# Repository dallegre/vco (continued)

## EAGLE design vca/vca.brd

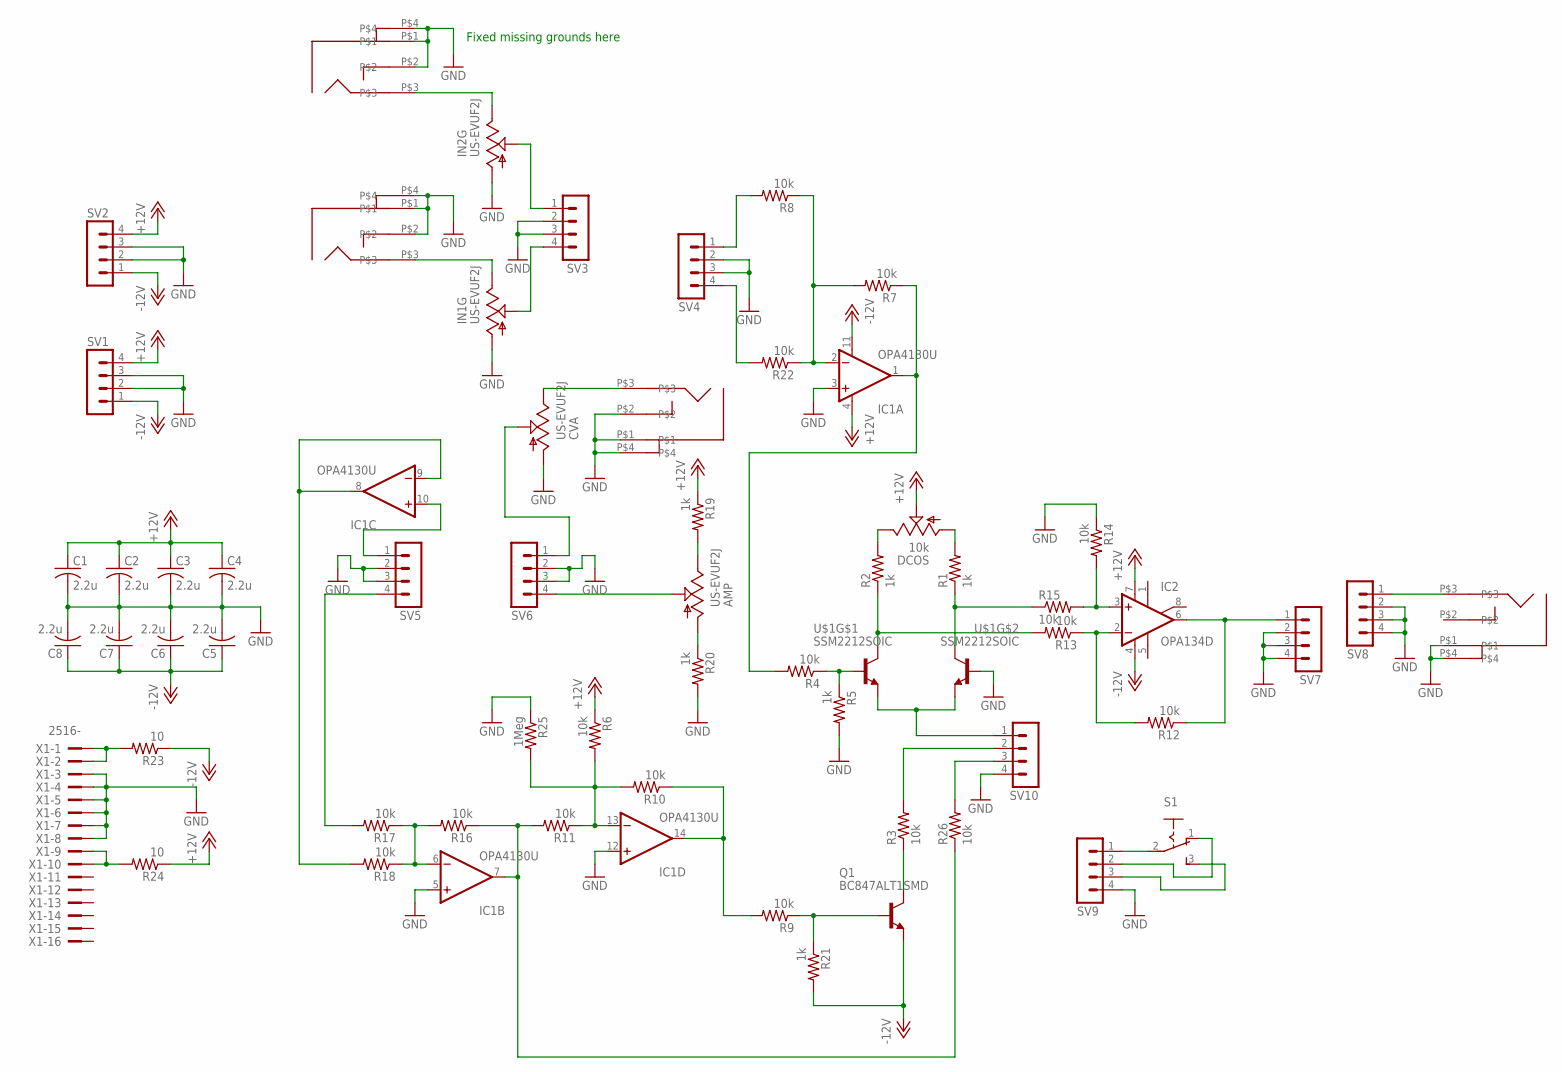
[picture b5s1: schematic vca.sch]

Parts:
AMP: US-EVUF2J; EVUFXJ
C1, C2, C3, C4, C5, C6, C7, C8: 2.2u; C0603
CVA: US-EVUF2J; EVUFXJ
CVIN: PJ301BM
DCOS: 10k; RJ9W
IC1: OPA4130U; SO14
IC2: OPA134D; SO08
IN1, IN2: PJ301BM
IN1G, IN2G: US-EVUF2J; EVUFXJ
OUT: PJ301BM
Q1: BC847ALT1SMD; SOT23
R1, R2, R5, R19, R20, R21: 1k; R0603
R3, R4, R6, R7, R8, R9, R10, R11, R12, R13, R14, R15, R16, R17, R18, R22, R26: 10k; R0603
R23, R24: 10; R0603
R25: 1Meg; R0603
S1: 255SB
SV1, SV2, SV3, SV4, SV5, SV6, SV7, SV8, SV9, SV10: MA04-1
U$1: SSM2212SOIC; SO08
X1: 2516-; PAK100/2500-16

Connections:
+12V: C1.1, C2.1, C3.1, C4.1, DCOS.S, IC1.4 (V+), IC2.7 (V+), R6.1, R19.1, R24.1, SV1.4, SV2.4
-12V: C5.1, C6.1, C7.1, C8.1, IC1.11 (V-), IC2.4 (V-), Q1.2 (E), R21.2, R23.1, SV1.1, SV2.1
GND: C1.2, C2.2, C3.2, C4.2, C5.2, C6.2, C7.2, C8.2, CVA.1 (A), CVIN.P$1, CVIN.P$2, CVIN.P$4, IC1.3 (+IN), IC1.5 (+IN), IC1.12 (+IN), IN1.P$1, IN1.P$2, IN1.P$4, IN1G.1 (A), IN2.P$1, IN2.P$2, IN2.P$4, IN2G.1 (A), OUT.P$1, OUT.P$4, R5.2, R14.1, R20.2, R25.1, SV1.2, SV1.3, SV2.2, SV2.3, SV3.2, SV3.3, SV4.2, SV4.3, SV5.2, SV5.3, SV6.2, SV6.3, SV7.2, SV7.3, SV7.4, SV8.2, SV8.3, SV8.4, SV9.4, SV10.4, U$1.7 (B), X1.3, X1.4, X1.5, X1.6, X1.7, X1.8
unnamed: SV10.1, U$1.3 (E), U$1.6 (E)
unnamed: R4.1, R5.1, U$1.2 (B)
unnamed: R2.1, R13.2, U$1.1 (C)
unnamed: R1.1, R15.1, U$1.8 (C)
unnamed: OUT.P$3, SV8.1
unnamed: IC1.8 (OUT), IC1.9 (-IN), R18.2
unnamed: Q1.3 (C), R3.1
unnamed: Q1.1 (B), R9.1, R21.1
unnamed: IC1.14 (OUT), R9.2, R10.1
unnamed: IC1.2 (-IN), R7.2, R8.1, R22.1
unnamed: IC1.1 (OUT), R4.2, R7.1
unnamed: IC1.13 (-IN), R6.2, R10.2, R11.1, R25.2
unnamed: IC2.3 (+IN), R14.2, R15.2
unnamed: DCOS.E, R2.2
unnamed: DCOS.A, R1.2
unnamed: IC2.2 (-IN), R12.2, R13.1
unnamed: IC2.6 (OUT), R12.1, SV7.1
unnamed: IN2G.2 (S), SV3.1
unnamed: IC1.6 (-IN), R16.2, R17.1, R18.1
unnamed: IN1G.2 (S), SV3.4
unnamed: AMP.3 (E), R19.2
unnamed: AMP.1 (A), R20.1
unnamed: R17.2, SV5.4
unnamed: IN1.P$3, IN1G.3 (E)
unnamed: CVA.3 (E), CVIN.P$3
unnamed: IN2.P$3, IN2G.3 (E)
unnamed: R8.2, SV4.1
unnamed: R22.2, SV4.4
unnamed: R23.2, X1.1, X1.2
unnamed: CVA.2 (S), SV6.1
unnamed: AMP.2 (S), SV6.4
unnamed: IC1.10 (+IN), SV5.1
unnamed: R24.2, X1.9, X1.10
unnamed: R3.2, SV10.2
unnamed: IC1.7 (OUT), R11.2, R16.1, R26.1
unnamed: S1.2, SV9.1
unnamed: R26.2, SV10.3
unnamed: S1.1 (O), SV9.2
unnamed: S1.3 (S), SV9.3

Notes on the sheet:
Fixed missing grounds here

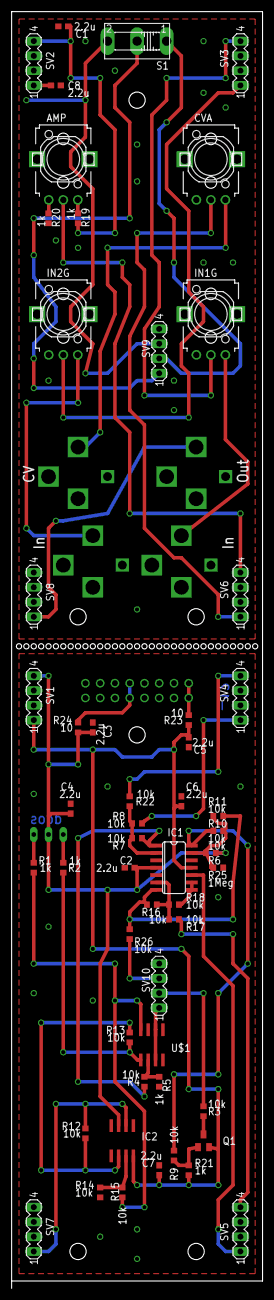
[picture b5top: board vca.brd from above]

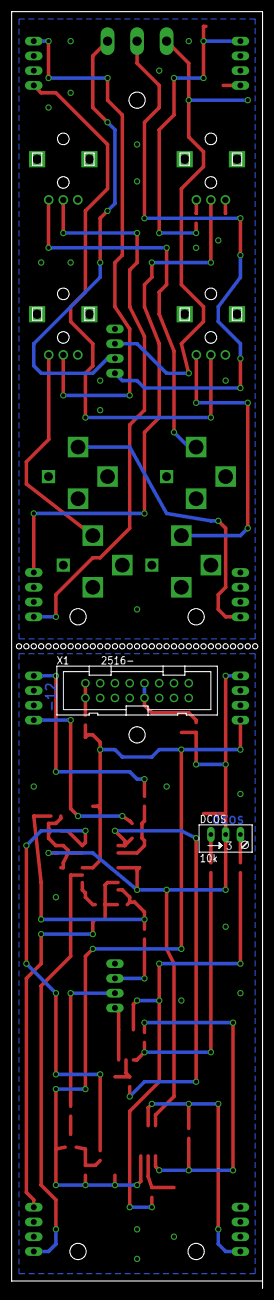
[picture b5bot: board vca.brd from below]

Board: 2 copper layers, 43.2 x 219.7 mm, 59 parts (2 on the bottom side), 42 nets.

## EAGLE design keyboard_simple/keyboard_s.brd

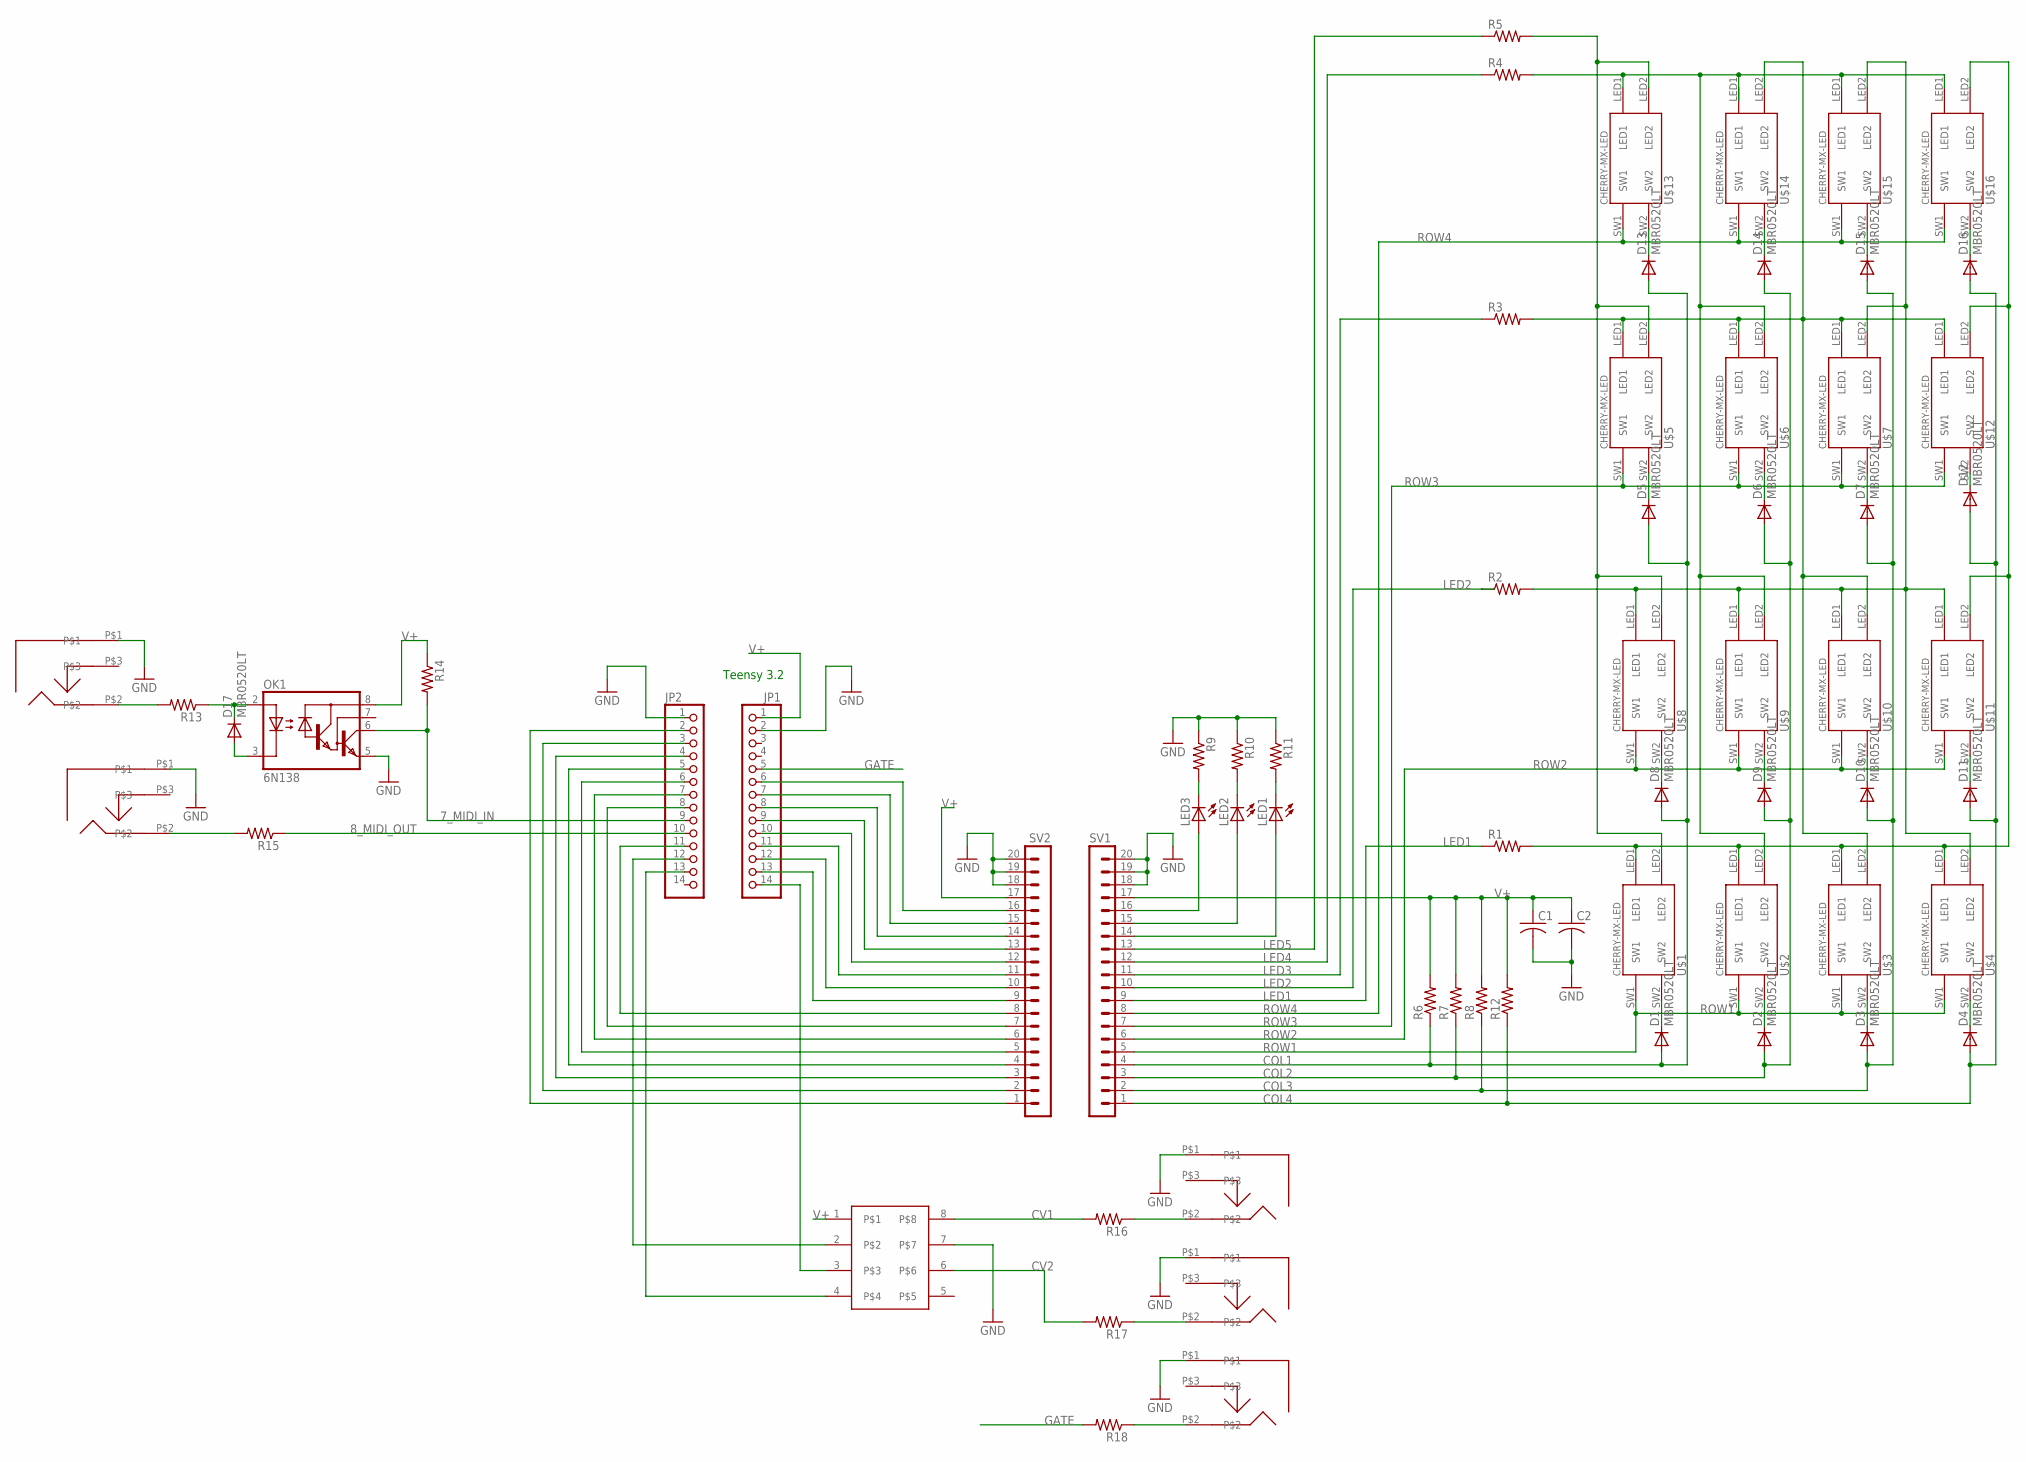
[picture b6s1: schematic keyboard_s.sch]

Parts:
C1, C2: C-USC0603; C0603
D1, D2, D3, D4, D5, D6, D7, D8, D9, D10, D11, D12, D13, D14, D15, D16, D17: MBR0520LT; SOD123
JP1, JP2: PINHD-1X14; 1X14
LED1, LED2, LED3: LED5MM
OK1: 6N138; DIL08
R1, R2, R3, R4, R5, R6, R7, R8, R9, R10, R11, R12, R13, R14, R15, R16, R17, R18: R-US_R0603; R0603
SV1, SV2: MA20-1
U$1, U$2, U$3, U$4, U$5, U$6, U$7, U$8, U$9, U$10, U$11, U$12, U$13, U$14, U$15, U$16: CHERRY-MX-LED
U$17: MCP4822; SO08
U$18, U$19, U$20, U$21, U$22: MJ3536N

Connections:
7_MIDI_IN: JP2.9, OK1.6 (VO), R14.2
8_MIDI_OUT: JP2.10, R15.1
COL1: D1.A, D5.A, D8.A, D13.A, R6.1, SV1.4
COL2: D2.A, D6.A, D9.A, D14.A, R7.1, SV1.3
COL3: D3.A, D7.A, D10.A, D15.A, R8.1, SV1.2
COL4: D4.A, D11.A, D12.A, D16.A, R12.1, SV1.1
CV1: R16.2, U$17.8
CV2: R17.2, U$17.6
GATE: JP1.5, R18.2
GND: C1.2, C2.2, JP1.2, JP2.1, OK1.5 (GND), R9.1, R10.1, R11.1, SV1.18, SV1.19, SV1.20, SV2.18, SV2.19, SV2.20, U$17.7, U$18.P$1, U$19.P$1, U$20.P$1, U$21.P$1, U$22.P$1
LED1: R1.1, SV1.9
LED2: R2.1, SV1.10
LED3: R3.1, SV1.11
LED4: R4.1, SV1.12
LED5: R5.1, SV1.13
unnamed: D8.C, U$8.SW2
unnamed: D9.C, U$9.SW2
unnamed: D10.C, U$10.SW2
unnamed: D11.C, U$11.SW2
unnamed: D12.C, U$12.SW2
unnamed: D13.C, U$13.SW2
unnamed: D14.C, U$14.SW2
unnamed: D7.C, U$7.SW2
unnamed: D6.C, U$6.SW2
unnamed: D5.C, U$5.SW2
unnamed: D4.C, U$4.SW2
unnamed: D3.C, U$3.SW2
unnamed: D2.C, U$2.SW2
unnamed: D1.C, U$1.SW2
unnamed: D15.C, U$15.SW2
unnamed: D16.C, U$16.SW2
unnamed: LED1.A, SV1.14
unnamed: D17.C, OK1.2 (A), R13.1
unnamed: R1.2, U$1.LED1, U$2.LED1, U$3.LED1, U$4.LED1, U$11.LED2, U$12.LED2, U$16.LED2
unnamed: D17.A, OK1.3 (C)
unnamed: LED2.A, SV1.15
unnamed: LED3.A, SV1.16
unnamed: R13.2, U$18.P$2
unnamed: JP1.14, U$17.3
unnamed: JP2.13, U$17.4
unnamed: JP2.12, U$17.2
unnamed: JP2.2, SV2.1
unnamed: JP2.3, SV2.2
unnamed: JP2.4, SV2.3
unnamed: JP2.5, SV2.4
unnamed: JP2.6, SV2.5
unnamed: JP2.7, SV2.6
unnamed: JP2.8, SV2.7
unnamed: JP2.11, SV2.8
unnamed: JP1.13, SV2.9
unnamed: JP1.12, SV2.10
unnamed: JP1.11, SV2.11
unnamed: JP1.10, SV2.12
unnamed: JP1.9, SV2.13
unnamed: JP1.8, SV2.14
unnamed: JP1.7, SV2.15
unnamed: JP1.6, SV2.16
unnamed: R15.2, U$19.P$2
unnamed: R16.1, U$20.P$2
unnamed: R17.1, U$21.P$2
unnamed: R18.1, U$22.P$2
unnamed: LED1.K (C), R11.2
unnamed: R3.2, U$3.LED2, U$5.LED1, U$6.LED1, U$7.LED1, U$10.LED2, U$12.LED1, U$14.LED2
unnamed: R5.2, U$1.LED2, U$5.LED2, U$8.LED2, U$13.LED2
unnamed: LED2.K (C), R10.2
unnamed: LED3.K (C), R9.2
unnamed: R4.2, U$2.LED2, U$6.LED2, U$9.LED2, U$13.LED1, U$15.LED1, U$16.LED1
unnamed: R2.2, U$4.LED2, U$7.LED2, U$8.LED1, U$9.LED1, U$10.LED1, U$11.LED1, U$15.LED2
ROW1: SV1.5, U$1.SW1, U$2.SW1, U$3.SW1, U$4.SW1
ROW2: SV1.6, U$8.SW1, U$9.SW1, U$10.SW1, U$11.SW1
ROW3: SV1.7, U$5.SW1, U$6.SW1, U$7.SW1, U$12.SW1
ROW4: SV1.8, U$13.SW1, U$14.SW1, U$15.SW1, U$16.SW1
V+: C1.1, C2.1, JP1.1, OK1.8 (VCC), R6.2, R7.2, R8.2, R12.2, R14.1, SV1.17, SV2.17

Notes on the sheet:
Teensy 3.2

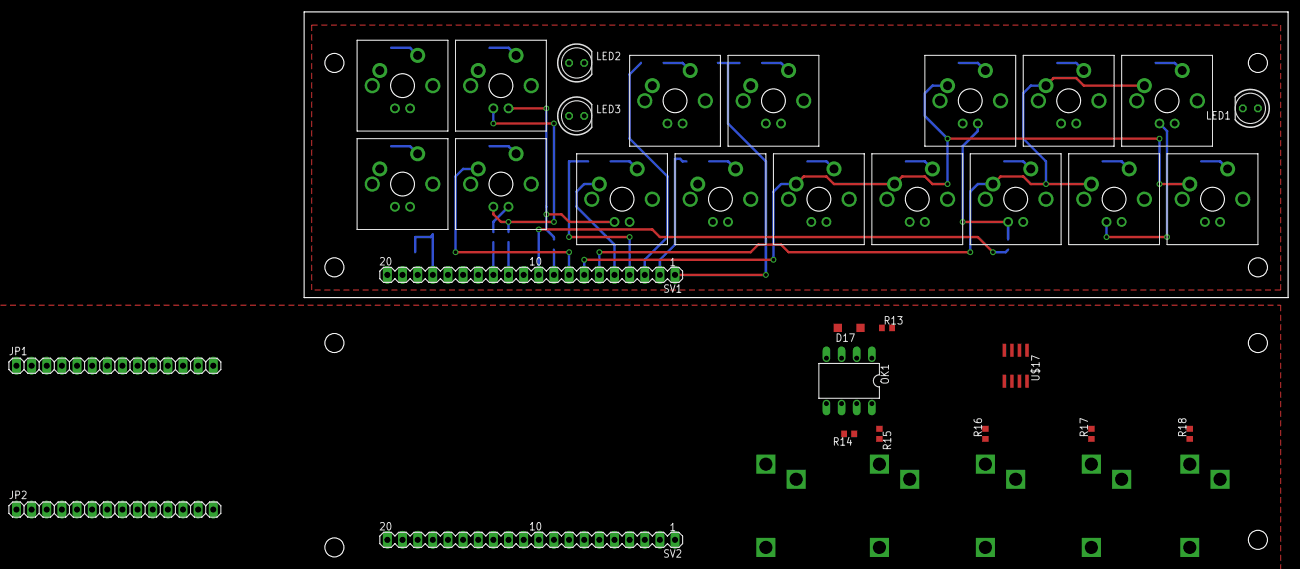
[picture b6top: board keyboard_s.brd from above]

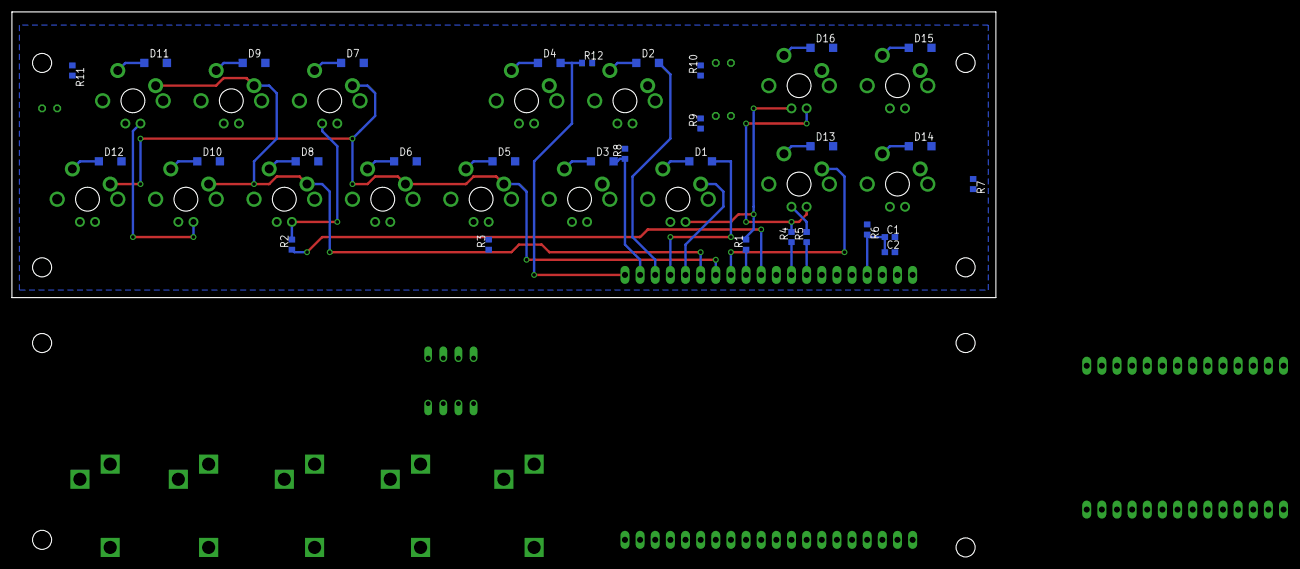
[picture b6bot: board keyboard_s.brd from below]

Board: 2 copper layers, 165.1 x 47.9 mm, 67 parts (30 on the bottom side), 73 nets.

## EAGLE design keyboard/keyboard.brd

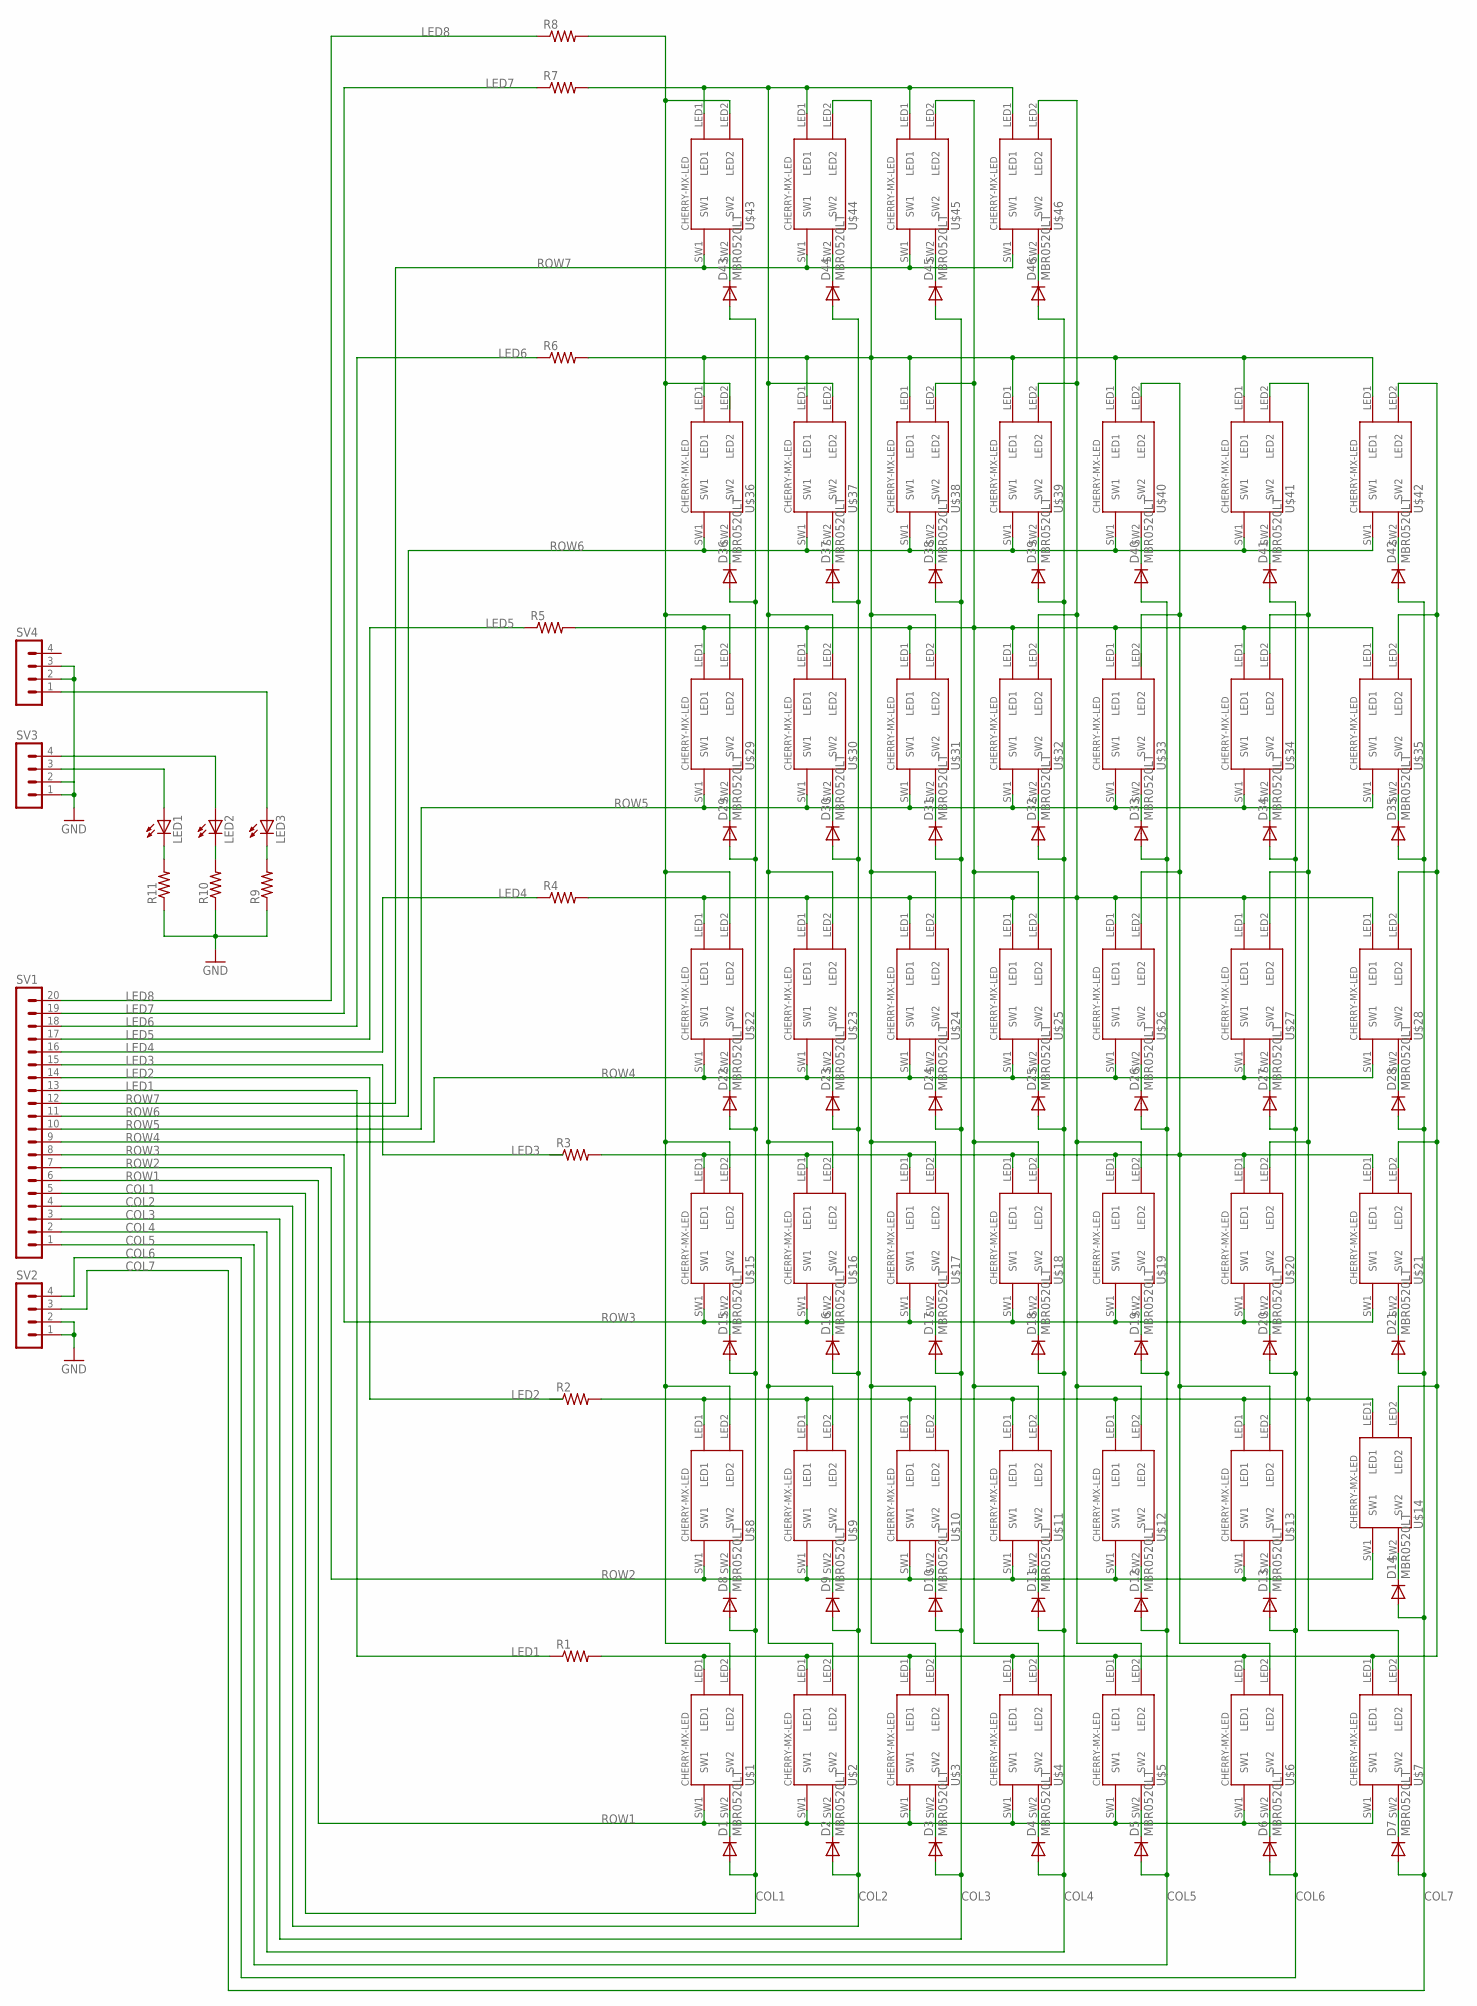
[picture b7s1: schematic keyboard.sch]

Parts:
D1, D2, D3, D4, D5, D6, D7, D8, D9, D10, D11, D12, D13, D14, D15, D16, D17, D18, D19, D20, D21, D22, D23, D24, D25, D26, D27, D28, D29, D30, D31, D32, D33, D34, D35, D36, D37, D38, D39, D40, D41, D42, D43, D44, D45, D46: MBR0520LT; SOD123
LED1, LED2, LED3: LED5MM
R1, R2, R3, R4, R5, R6, R7, R8, R9, R10, R11: R-US_R0603; R0603
SV1: MA20-1
SV2, SV3, SV4: MA04-1
U$1, U$2, U$3, U$4, U$5, U$6, U$7, U$8, U$9, U$10, U$11, U$12, U$13, U$14, U$15, U$16, U$17, U$18, U$19, U$20, U$21, U$22, U$23, U$24, U$25, U$26, U$27, U$28, U$29, U$30, U$31, U$32, U$33, U$34, U$35, U$36, U$37, U$38, U$39, U$40, U$41, U$42, U$43, U$44, U$45, U$46: CHERRY-MX-LED

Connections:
COL1: D1.A, D8.A, D15.A, D22.A, D29.A, D36.A, D43.A, SV1.5
COL2: D2.A, D9.A, D16.A, D23.A, D30.A, D37.A, D44.A, SV1.4
COL3: D3.A, D10.A, D17.A, D24.A, D31.A, D38.A, D45.A, SV1.3
COL4: D4.A, D11.A, D18.A, D25.A, D32.A, D39.A, D46.A, SV1.2
COL5: D5.A, D12.A, D19.A, D26.A, D33.A, D40.A, SV1.1
COL6: D6.A, D13.A, D20.A, D27.A, D34.A, D41.A
COL7: D7.A, D14.A, D21.A, D28.A, D35.A, D42.A, SV2.3
GND: R9.1, R10.1, R11.1, SV2.1, SV2.2, SV3.1, SV3.2, SV4.2, SV4.3
LED1: R1.1, SV1.13
LED2: SV1.14
LED3: SV1.15
LED4: R4.1, SV1.16
LED5: R5.1, SV1.17
LED6: R6.1, SV1.18
LED7: R7.1, SV1.19
LED8: R8.1, SV1.20
unnamed: D8.C, U$8.SW2
unnamed: D9.C, U$9.SW2
unnamed: D10.C, U$10.SW2
unnamed: D11.C, U$11.SW2
unnamed: D12.C, U$12.SW2
unnamed: D13.C, U$13.SW2
unnamed: D14.C, U$14.SW2
unnamed: D7.C, U$7.SW2
unnamed: D6.C, U$6.SW2
unnamed: D5.C, U$5.SW2
unnamed: D4.C, U$4.SW2
unnamed: D3.C, U$3.SW2
unnamed: D2.C, U$2.SW2
unnamed: D1.C, U$1.SW2
unnamed: D15.C, U$15.SW2
unnamed: D16.C, U$16.SW2
unnamed: D17.C, U$17.SW2
unnamed: D18.C, U$18.SW2
unnamed: D19.C, U$19.SW2
unnamed: D20.C, U$20.SW2
unnamed: D21.C, U$21.SW2
unnamed: D27.C, U$27.SW2
unnamed: D28.C, U$28.SW2
unnamed: D29.C, U$29.SW2
unnamed: D30.C, U$30.SW2
unnamed: D31.C, U$31.SW2
unnamed: D32.C, U$32.SW2
unnamed: D33.C, U$33.SW2
unnamed: D34.C, U$34.SW2
unnamed: D35.C, U$35.SW2
unnamed: D36.C, U$36.SW2
unnamed: D37.C, U$37.SW2
unnamed: D38.C, U$38.SW2
unnamed: D39.C, U$39.SW2
unnamed: D40.C, U$40.SW2
unnamed: D41.C, U$41.SW2
unnamed: D42.C, U$42.SW2
unnamed: D43.C, U$43.SW2
unnamed: D44.C, U$44.SW2
unnamed: D45.C, U$45.SW2
unnamed: D46.C, U$46.SW2
unnamed: LED1.K (C), R11.2
unnamed: R8.2, U$1.LED2, U$8.LED2, U$15.LED2, U$22.LED2, U$29.LED2, U$43.LED2
unnamed: R1.2, U$1.LED1, U$2.LED1, U$3.LED1, U$4.LED1, U$5.LED1, U$6.LED1, U$7.LED1, U$14.LED2, U$21.LED2, U$28.LED2, U$35.LED2, U$42.LED2
unnamed: R4.2, U$5.LED2, U$12.LED2, U$19.LED2, U$22.LED1, U$23.LED1, U$24.LED1, U$25.LED1, U$26.LED1, U$27.LED1, U$28.LED1, U$32.LED2, U$39.LED2, U$46.LED2
unnamed: R5.2, U$4.LED2, U$11.LED2, U$18.LED2, U$25.LED2, U$29.LED1, U$30.LED1, U$31.LED1, U$32.LED1, U$33.LED1, U$34.LED1, U$35.LED1, U$38.LED2, U$45.LED2
unnamed: R6.2, U$3.LED2, U$10.LED2, U$17.LED2, U$24.LED2, U$31.LED2, U$36.LED1, U$37.LED1, U$38.LED1, U$39.LED1, U$40.LED1, U$41.LED1, U$42.LED1, U$44.LED2
unnamed: LED2.K (C), R10.2
unnamed: LED3.K (C), R9.2
unnamed: LED1.A, SV3.3
unnamed: LED2.A, SV3.4
unnamed: LED3.A, SV4.1
unnamed: R7.2, U$2.LED2, U$9.LED2, U$16.LED2, U$23.LED2, U$30.LED2, U$37.LED2, U$43.LED1, U$44.LED1, U$45.LED1, U$46.LED1
unnamed: R2.2, U$7.LED2, U$8.LED1, U$9.LED1, U$10.LED1, U$11.LED1, U$13.LED1, U$14.LED1, U$20.LED2, U$27.LED2, U$34.LED2, U$41.LED2
unnamed: R3.2, U$6.LED2, U$13.LED2, U$15.LED1, U$16.LED1, U$17.LED1, U$18.LED1, U$19.LED1, U$20.LED1, U$21.LED1, U$26.LED2, U$40.LED2
ROW1: SV1.6, U$1.SW1, U$2.SW1, U$3.SW1, U$4.SW1, U$5.SW1, U$6.SW1, U$7.SW1
ROW2: SV1.7, U$8.SW1, U$9.SW1, U$10.SW1, U$11.SW1, U$12.SW1, U$13.SW1, U$14.SW1
ROW3: SV1.8, U$15.SW1, U$16.SW1, U$17.SW1, U$18.SW1, U$19.SW1, U$20.SW1, U$21.SW1
ROW4: SV1.9, U$22.SW1, U$23.SW1, U$24.SW1, U$25.SW1, U$26.SW1, U$27.SW1, U$28.SW1
ROW5: SV1.10, U$29.SW1, U$30.SW1, U$31.SW1, U$32.SW1, U$33.SW1, U$34.SW1, U$35.SW1
ROW6: SV1.11, U$36.SW1, U$37.SW1, U$38.SW1, U$39.SW1, U$40.SW1, U$41.SW1, U$42.SW1
ROW7: SV1.12, U$43.SW1, U$44.SW1, U$45.SW1, U$46.SW1

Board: 2 copper layers, 110 parts (57 on the bottom side), 76 nets, no tracks yet.

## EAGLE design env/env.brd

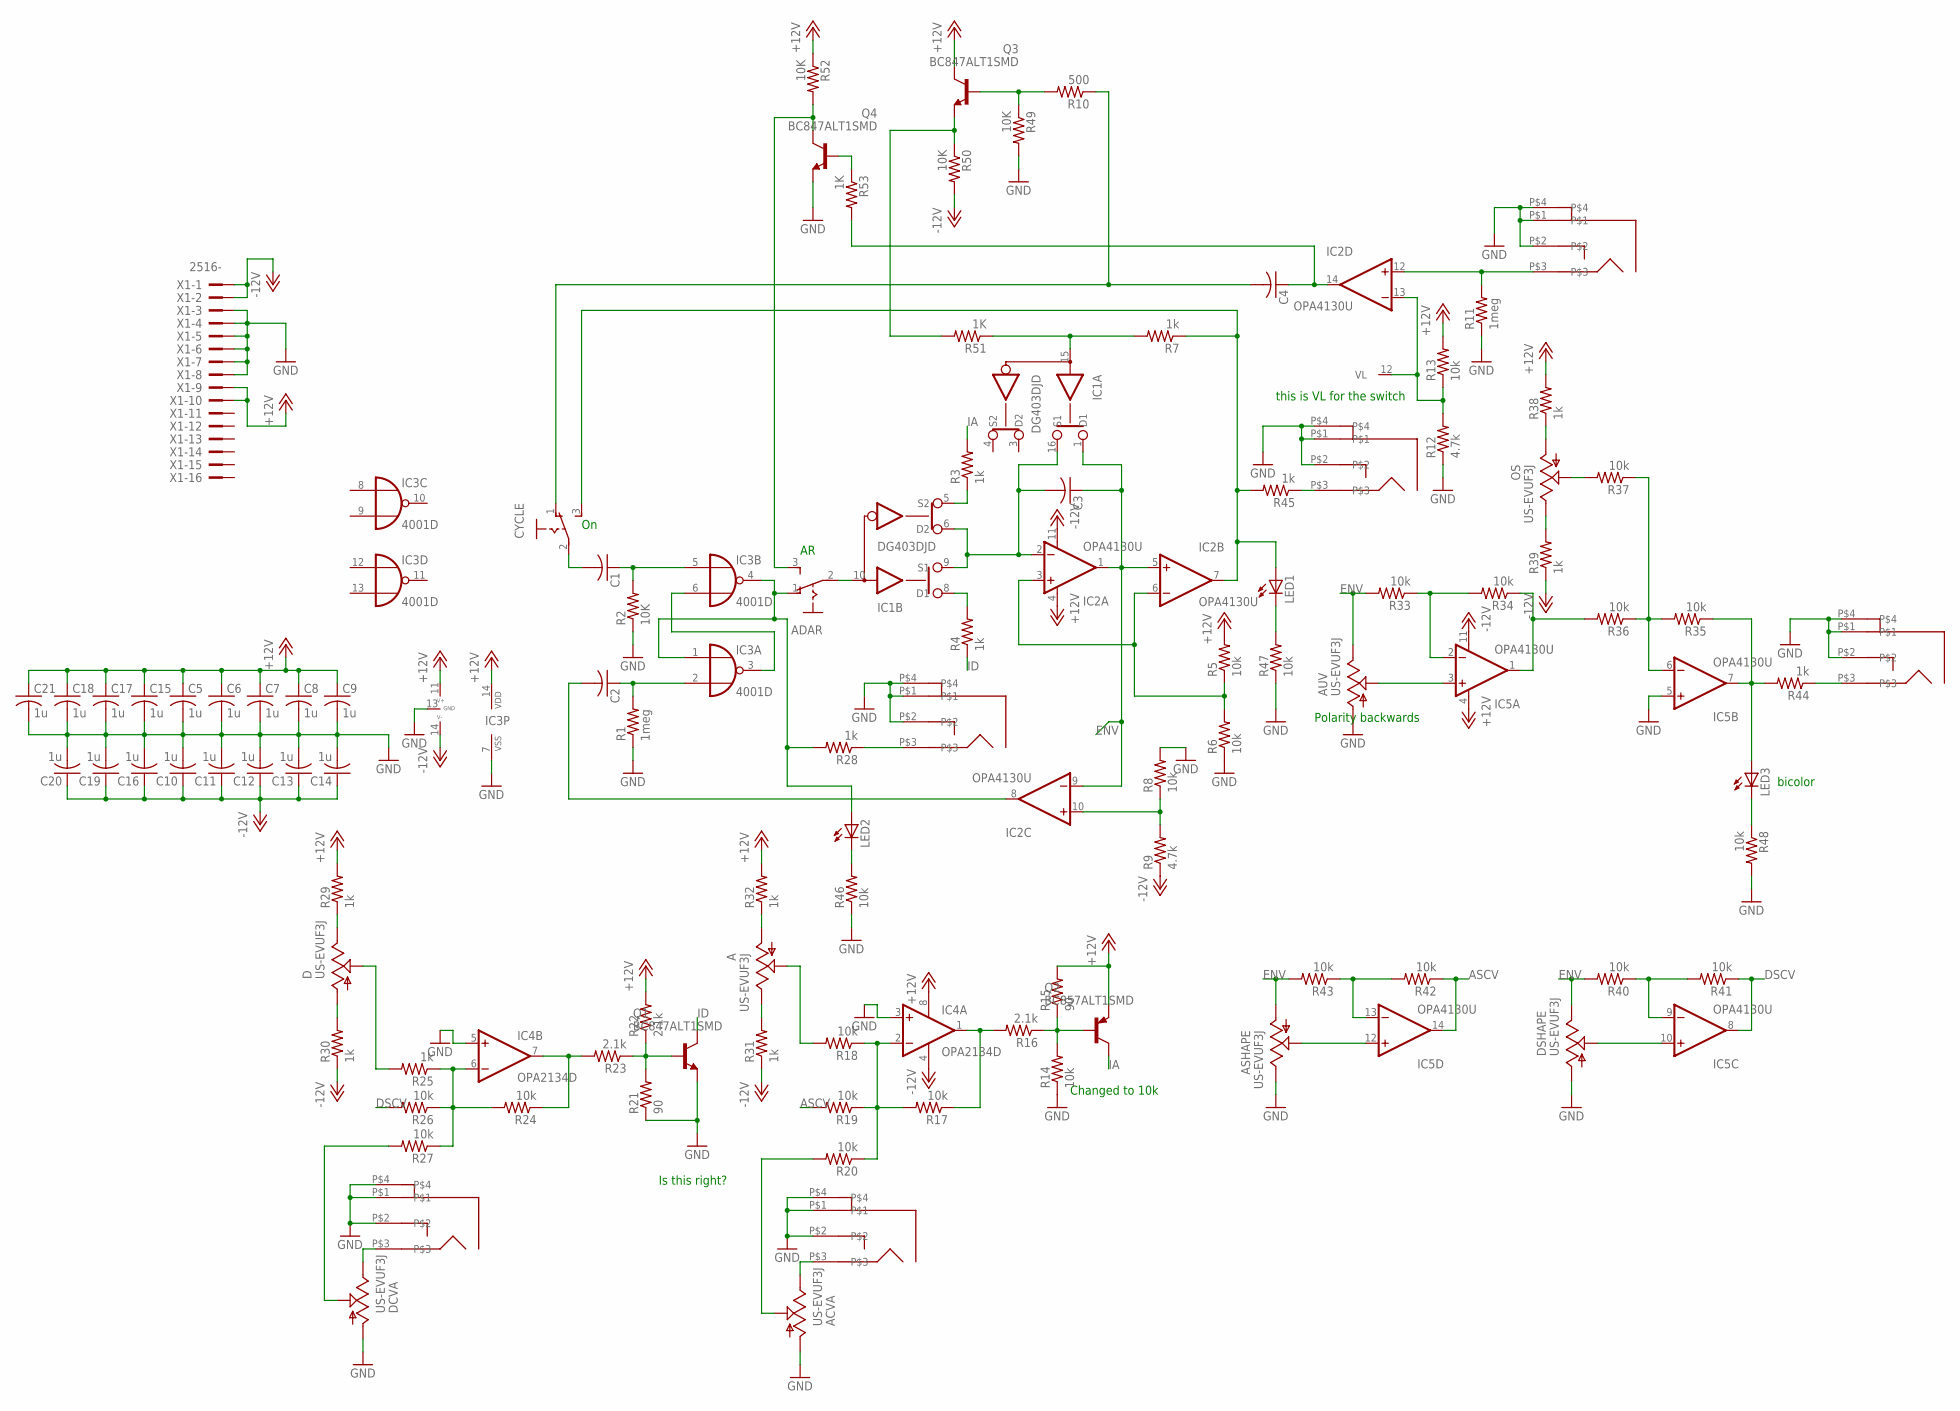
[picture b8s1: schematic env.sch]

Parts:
A: US-EVUF3J; EVUFXJ
ACV: PJ301BM
ACVA: US-EVUF3J; EVUFXJ
ADAR: 255SB
ASHAPE: US-EVUF3J; EVUFXJ
AUV: US-EVUF3J; EVUFXJ
C1, C2, C3, C4: C-USC0603; C0603
C5, C6, C7, C8, C9, C10, C11, C12, C13, C14, C15, C16, C17, C18, C19, C20, C21: 1u; C0603
CVOUT: PJ301BM
CYCLE: 255SB
D: US-EVUF3J; EVUFXJ
DCV: PJ301BM
DCVA: US-EVUF3J; EVUFXJ
DSHAPE: US-EVUF3J; EVUFXJ
EOF: PJ301BM
EOR: PJ301BM
GATE: PJ301BM
IC1: DG403DJD; SO16
IC2, IC5: OPA4130U; SO14
IC3: 4001D; SO14
IC4: OPA2134D; SOIC8
LED1, LED2, LED3: LED5MM
OS: US-EVUF3J; EVUFXJ
Q1, Q3, Q4: BC847ALT1SMD; SOT23
Q2: BC857ALT1SMD; SOT23-BEC
R1, R11: 1meg; R0603
R2, R49, R50, R52: 10K; R0603
R3, R4, R7, R25, R28, R29, R30, R31, R32, R38, R39, R44, R45: 1k; R0603
R5, R6, R8, R13, R14, R17, R18, R19, R20, R24, R26, R27, R33, R34, R35, R36, R37, R40, R41, R42, R43, R46, R47, R48: 10k; R0603
R9, R12: 4.7k; R0603
R10: 500; R0603
R15, R21: 90; R0603
R16, R22, R23: 2.1k; R0603
R51, R53: 1K; R0603
X1: 2516-; PAK100/2500-16

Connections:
+12V: C5.1, C6.1, C7.1, C8.1, C9.1, C15.1, C17.1, C18.1, C21.1, IC1.11 (V+), IC2.4 (V+), IC3.14 (VDD), IC4.8 (V+), IC5.4 (V+), Q2.E, Q3.3 (C), R5.2, R13.2, R15.2, R22.2, R29.2, R32.2, R38.2, R52.1, X1.9, X1.10
-12V: C10.1, C11.1, C12.1, C13.1, C14.1, C16.1, C19.1, C20.1, IC1.14 (V-), IC2.11 (V-), IC4.4 (V-), IC5.11 (V-), R9.1, R30.1, R31.1, R39.1, R50.2, X1.1, X1.2
ASCV: IC5.14 (OUT), R19.2, R42.1
DSCV: IC5.8 (OUT), R26.2, R41.1
ENV: ASHAPE.1 (A), AUV.3 (E), C3.1, DSHAPE.3 (E), IC1.1 (D1), IC2.1 (OUT), IC2.5 (+IN), IC2.9 (-IN), R33.2, R40.2, R43.2
GND: ACV.P$1, ACV.P$2, ACV.P$4, ACVA.1 (A), ASHAPE.3 (E), AUV.1 (A), C5.2, C6.2, C7.2, C8.2, C9.2, C10.2, C11.2, C12.2, C13.2, C14.2, C15.2, C16.2, C17.2, C18.2, C19.2, C20.2, C21.2, CVOUT.P$1, CVOUT.P$2, CVOUT.P$4, DCV.P$1, DCV.P$2, DCV.P$4, DCVA.1 (A), DSHAPE.1 (A), EOF.P$1, EOF.P$2, EOF.P$4, EOR.P$1, EOR.P$2, EOR.P$4, GATE.P$1, GATE.P$2, GATE.P$4, IC1.13 (GND), IC3.7 (VSS), IC4.3 (+IN), IC4.5 (+IN), IC5.5 (+IN), Q1.2 (E), Q4.2 (E), R1.1, R2.1, R6.1, R8.2, R11.1, R12.1, R14.1, R21.1, R46.1, R47.1, R48.2, R49.2, X1.3, X1.4, X1.5, X1.6, X1.7, X1.8
IA: Q2.C, R3.2
ID: Q1.3 (C), R4.1
unnamed: IC3.3 (O), IC3.6 (I1)
unnamed: ADAR.1 (O), IC3.1 (I0), IC3.4 (O), LED2.A, R28.2
unnamed: C2.1, IC3.2 (I1), R1.2
unnamed: C1.1, IC3.5 (I0), R2.2
unnamed: C3.2, IC1.6 (D2), IC1.9 (S1), IC1.16 (S1), IC2.2 (-IN)
unnamed: IC1.8 (D1), R4.2
unnamed: IC1.5 (S2), R3.1
unnamed: IC2.10 (+IN), R8.1, R9.2
unnamed: CYCLE.3 (S), IC2.7 (OUT), LED1.A, R7.1, R45.2
unnamed: AUV.2 (S), IC5.3 (+IN)
unnamed: Q3.2 (E), R50.1, R51.2
unnamed: C2.2, IC2.8 (OUT)
unnamed: IC2.3 (+IN), IC2.6 (-IN), R5.1, R6.2
unnamed: ADAR.3 (S), Q4.3 (C), R52.2
unnamed: Q2.B, R14.2, R15.1, R16.1
unnamed: GATE.P$3, IC2.12 (+IN), R11.2
unnamed: IC1.12 (VL), IC2.13 (-IN), R12.2, R13.1
unnamed: ADAR.2, IC1.10 (IN)
unnamed: C1.2, CYCLE.2
unnamed: C4.1, IC2.14 (OUT), R53.2
unnamed: IC4.1 (OUT), R16.2, R17.1
unnamed: IC4.7 (OUT), R23.2, R24.1
unnamed: IC4.2 (-IN), R17.2, R18.1, R19.1, R20.1
unnamed: IC4.6 (-IN), R24.2, R25.1, R26.1, R27.1
unnamed: D.3 (E), R29.1
unnamed: Q1.1 (B), R21.2, R22.1, R23.1
unnamed: IC5.6 (-IN), R35.2, R36.1, R37.1
unnamed: A.1 (A), R32.1
unnamed: D.1 (A), R30.2
unnamed: A.3 (E), R31.2
unnamed: D.2 (S), R25.2
unnamed: A.2 (S), R18.2
unnamed: IC5.1 (OUT), R34.1, R36.2
unnamed: IC5.2 (-IN), R33.1, R34.2
unnamed: CVOUT.P$3, R44.1
unnamed: IC5.7 (OUT), LED3.A, R35.1, R44.2
unnamed: OS.1 (A), R38.1
unnamed: ACV.P$3, ACVA.3 (E)
unnamed: OS.3 (E), R39.2
unnamed: OS.2 (S), R37.2
unnamed: IC5.13 (-IN), R42.2, R43.1
unnamed: IC5.9 (-IN), R40.1, R41.2
unnamed: LED2.K (C), R46.2
unnamed: DCV.P$3, DCVA.3 (E)
unnamed: ASHAPE.2 (S), IC5.12 (+IN)
unnamed: DCVA.2 (S), R27.2
unnamed: EOR.P$3, R28.1
unnamed: DSHAPE.2 (S), IC5.10 (+IN)
unnamed: EOF.P$3, R45.1
unnamed: ACVA.2 (S), R20.2
unnamed: Q3.1 (B), R10.2, R49.1
unnamed: LED1.K (C), R47.2
unnamed: IC1.15 (IN), R7.2, R51.1
unnamed: C4.2, CYCLE.1 (O), R10.1
unnamed: Q4.1 (B), R53.1
unnamed: LED3.K (C), R48.1

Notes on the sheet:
Is this right?
Changed to 10k
Polarity backwards
bicolor
this is VL for the switch

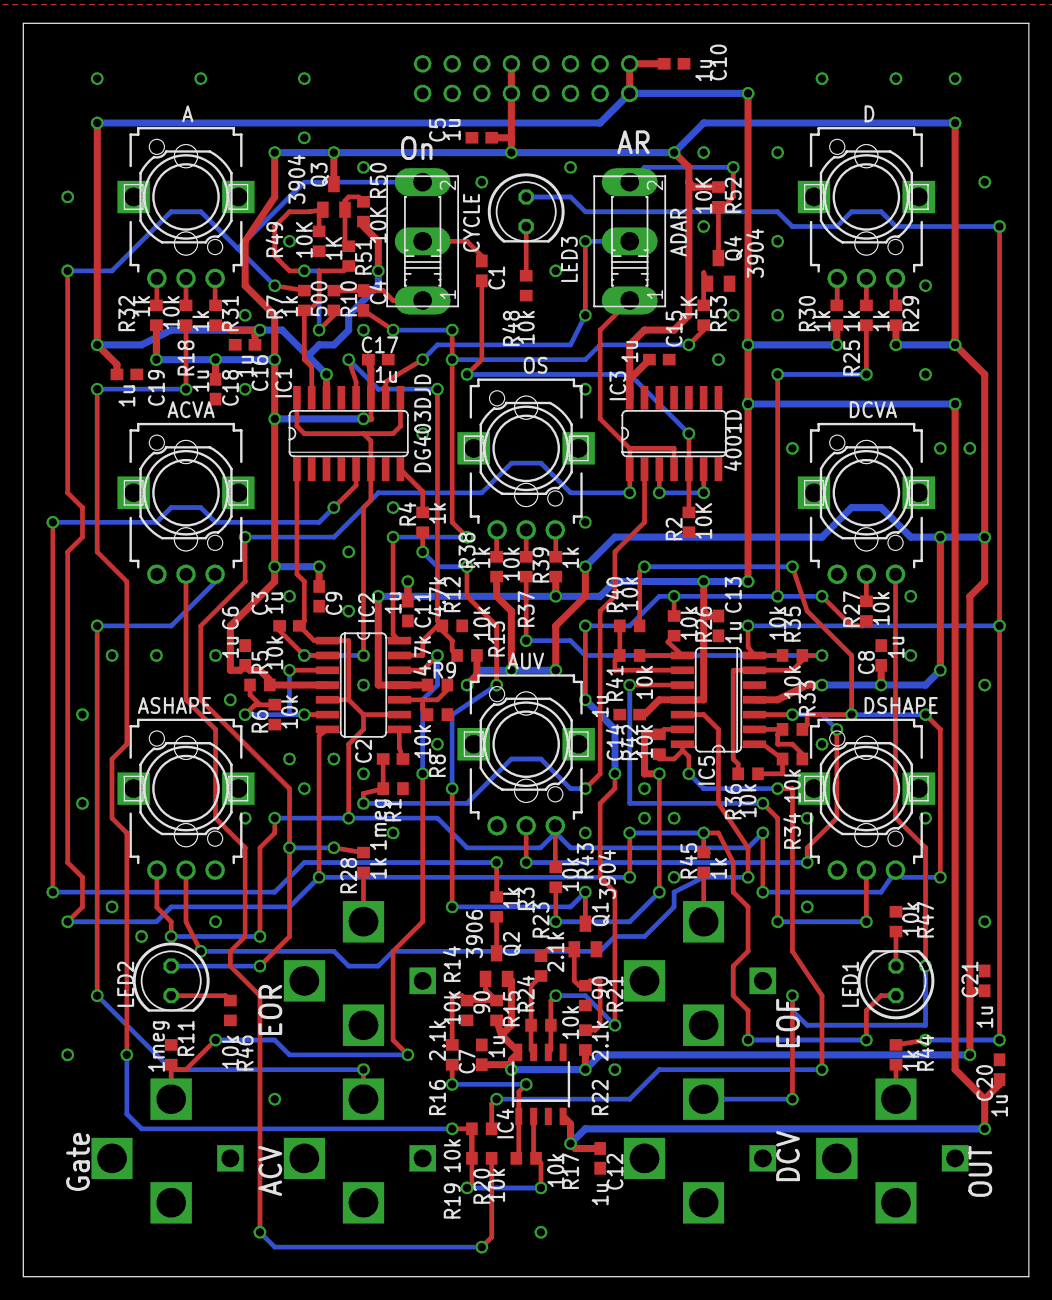
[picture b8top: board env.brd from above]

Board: 2 copper layers, 86.3 x 107.6 mm, 103 parts (1 on the bottom side), 64 nets.
